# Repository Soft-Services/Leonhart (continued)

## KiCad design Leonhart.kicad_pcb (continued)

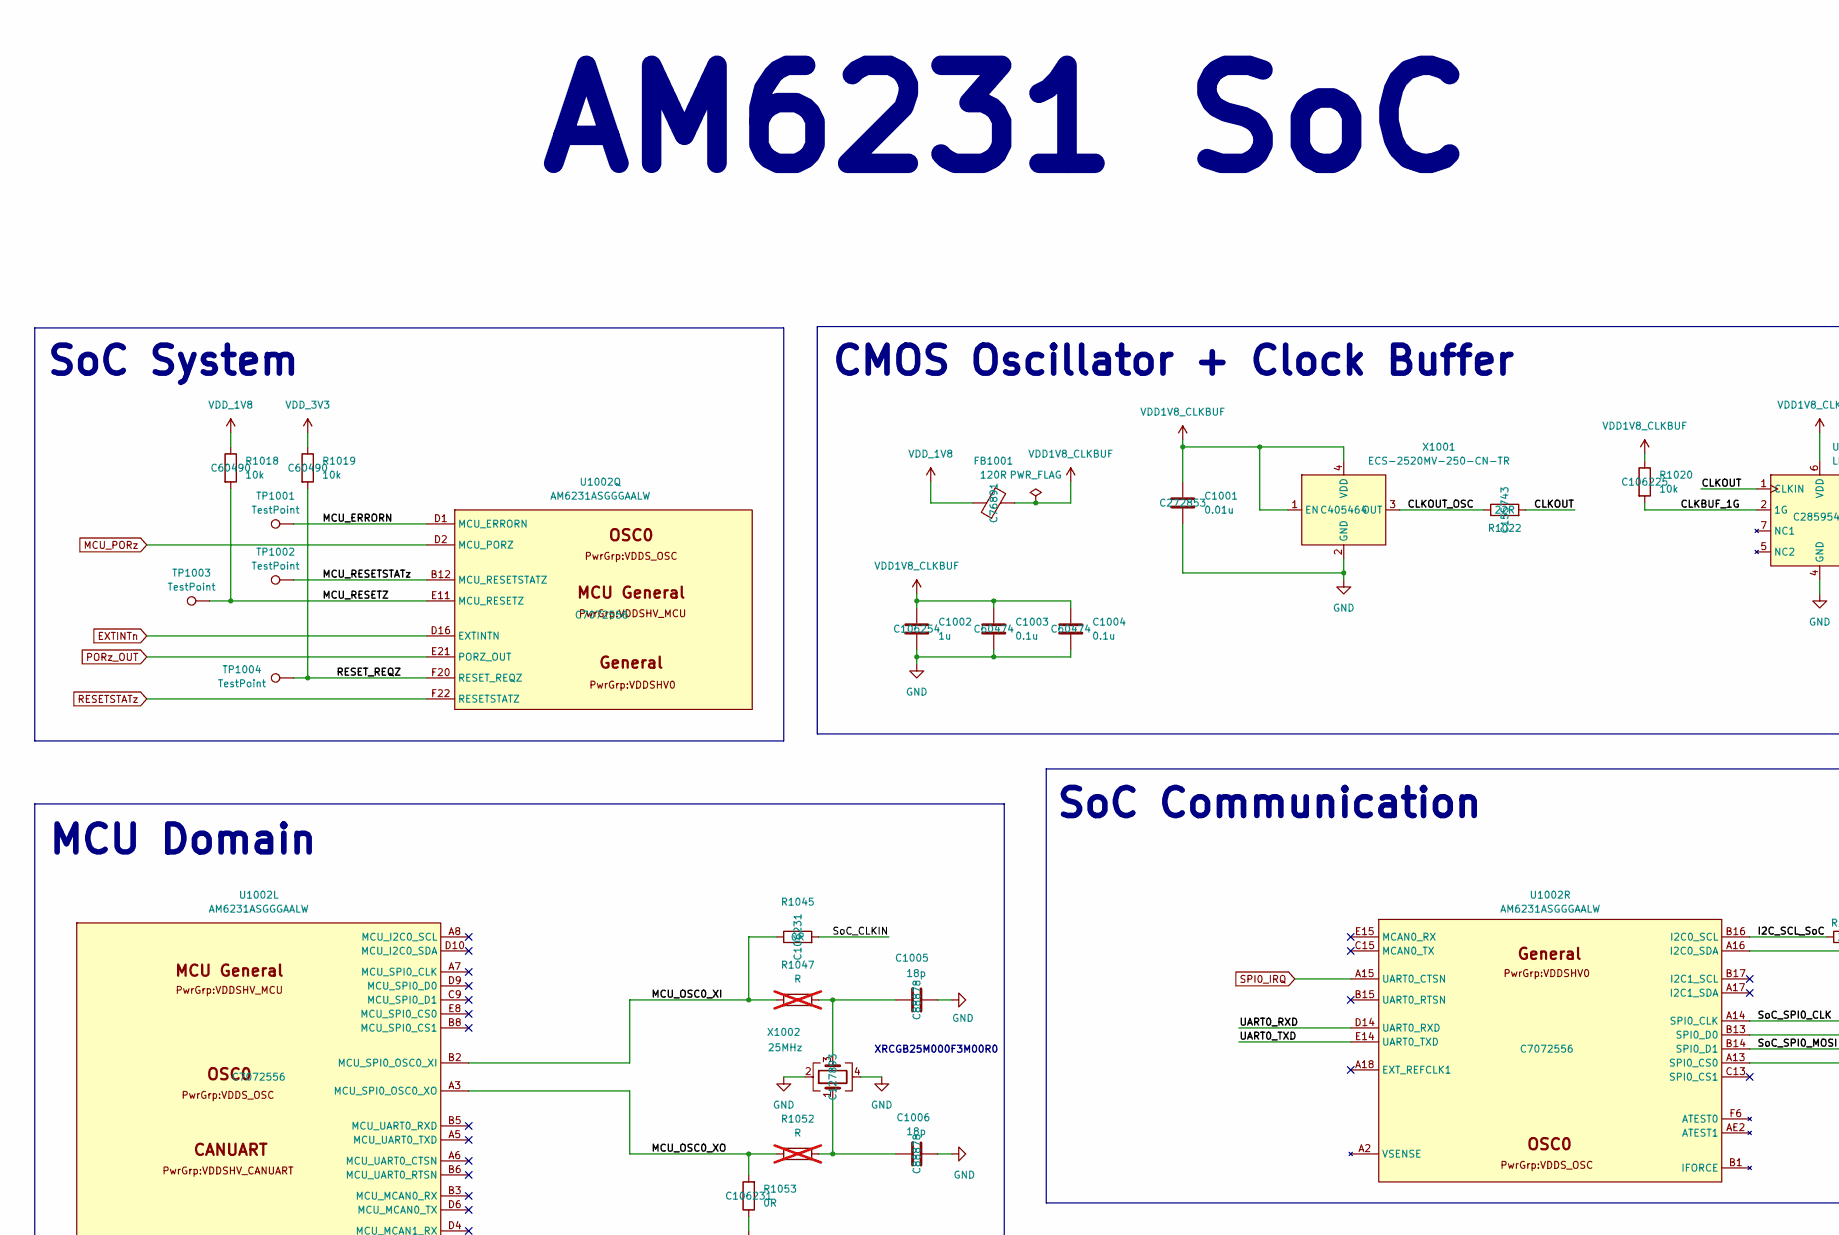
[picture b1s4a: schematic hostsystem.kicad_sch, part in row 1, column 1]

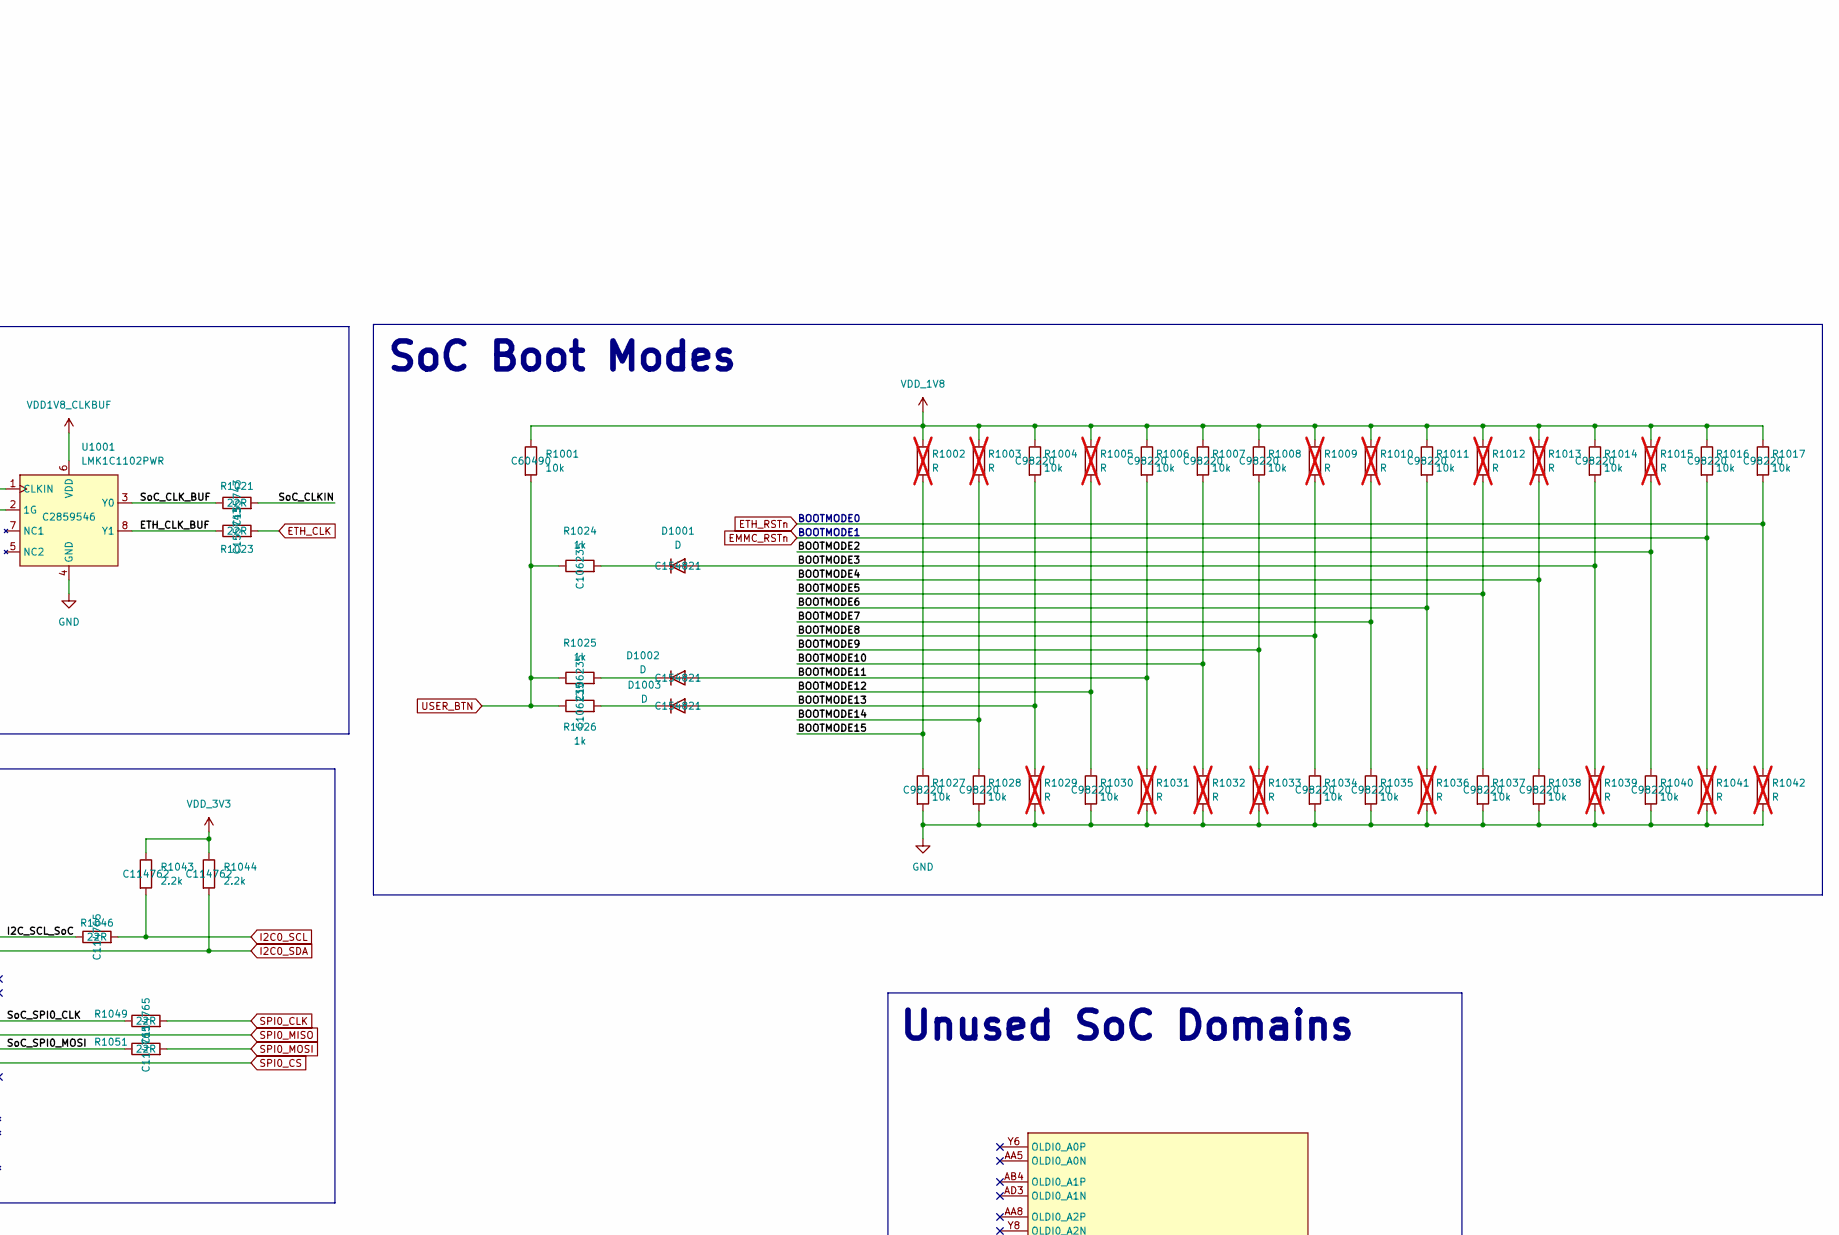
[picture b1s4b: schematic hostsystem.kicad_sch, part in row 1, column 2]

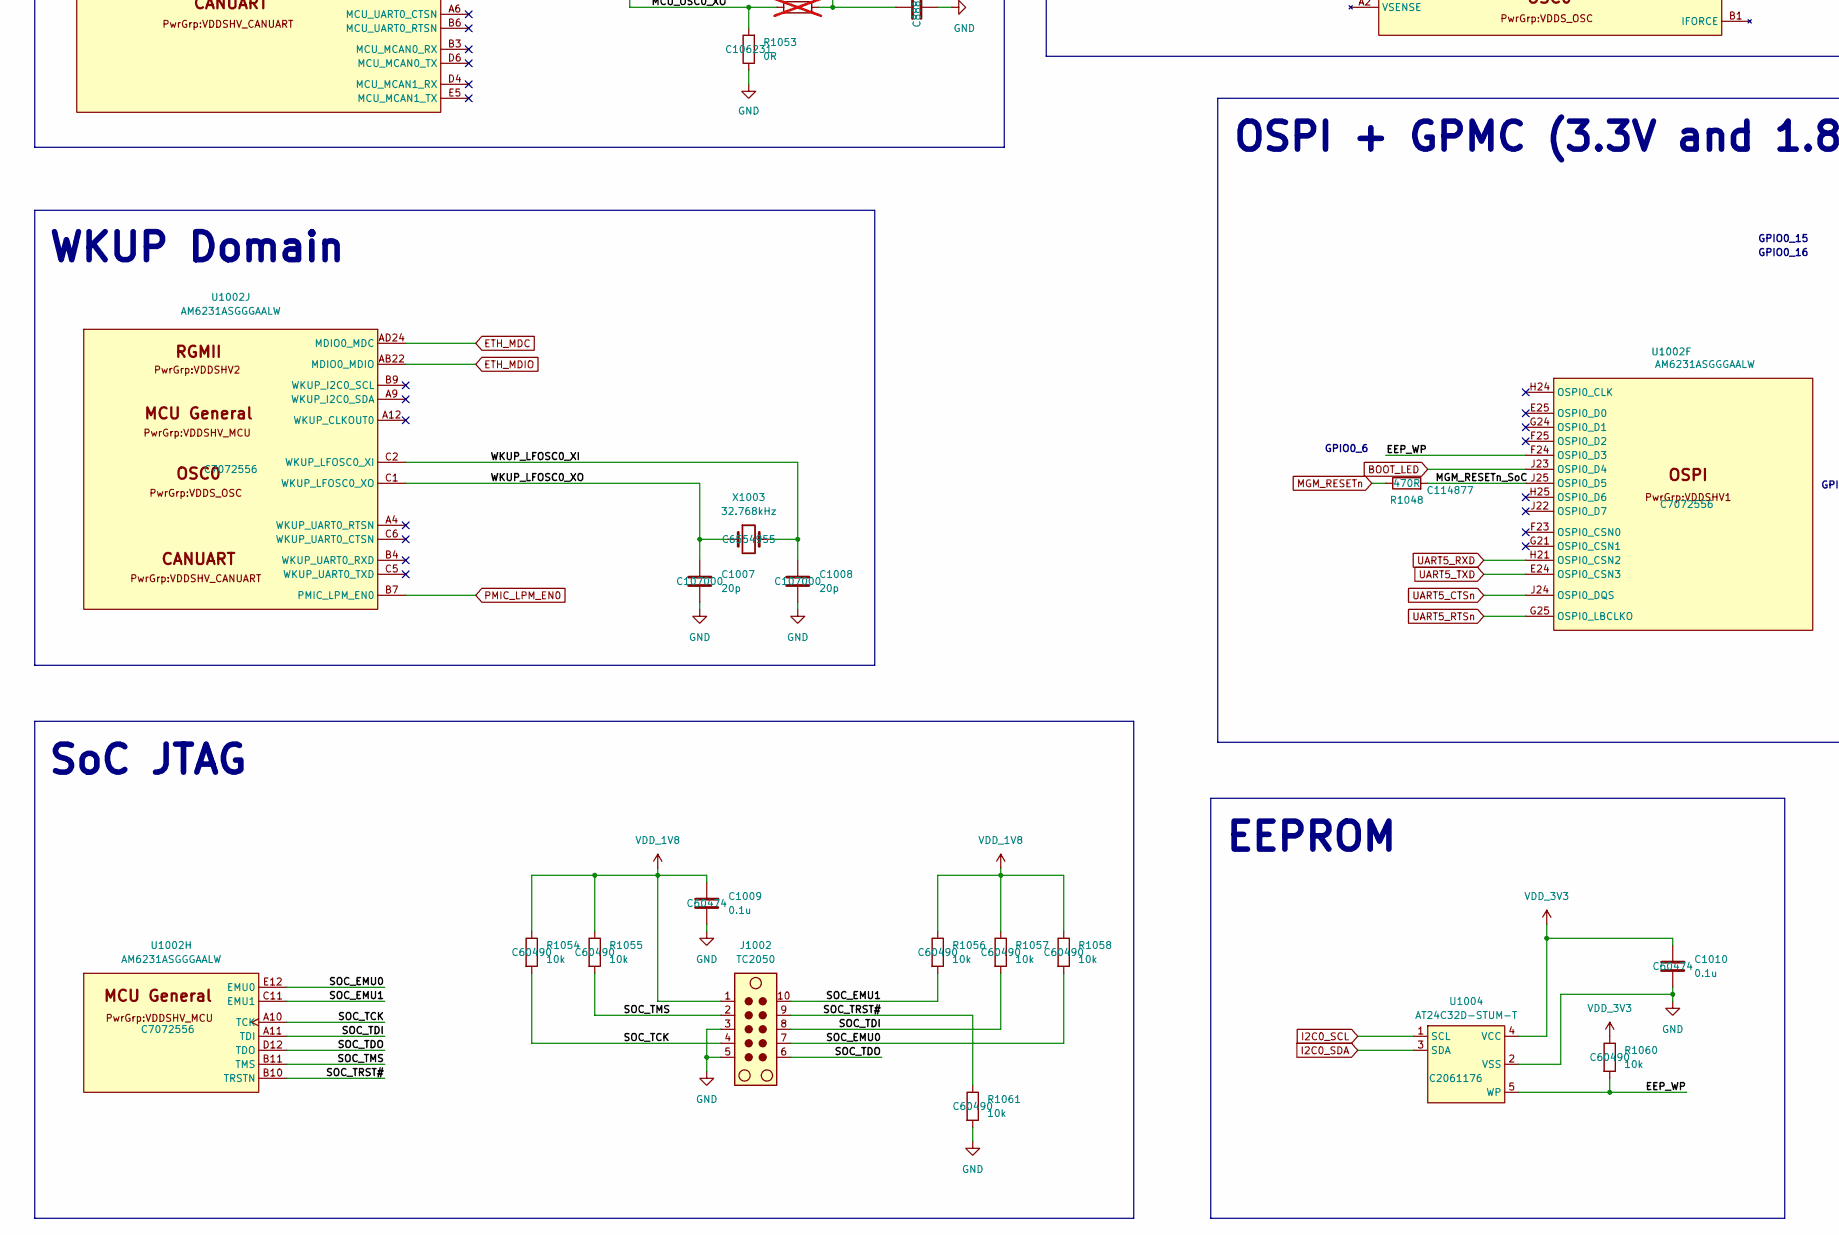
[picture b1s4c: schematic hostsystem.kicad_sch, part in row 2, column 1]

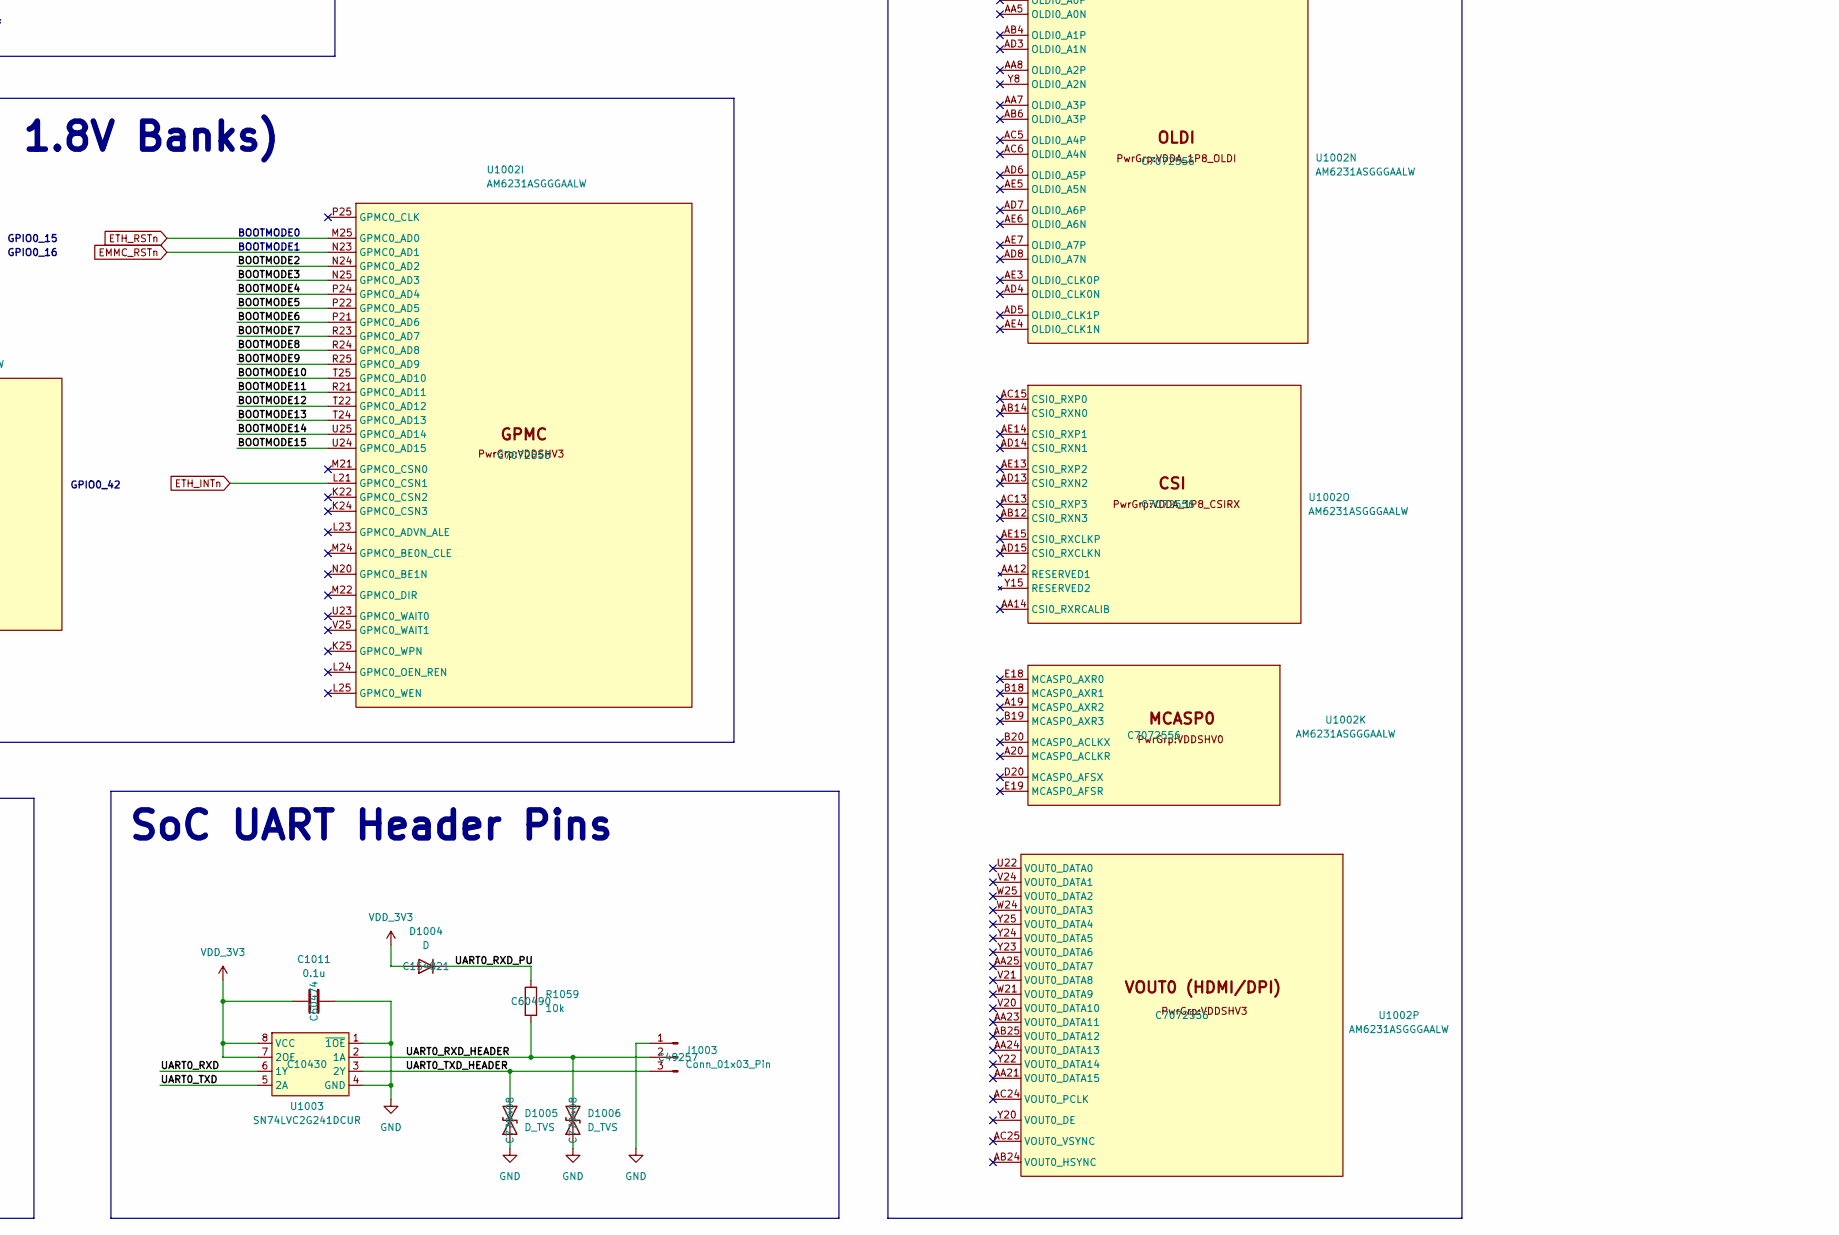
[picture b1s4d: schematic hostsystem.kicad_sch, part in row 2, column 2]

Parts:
C1001: 0.01u; C_0201_0603Metric; JLCPCB Part# C272853
C1002: 1u; C_0402_1005Metric; JLCPCB Part# C106254
C1003, C1004, C1009, C1010, C1011: 0.1u; C_0402_1005Metric; JLCPCB Part# C60474
C1005, C1006: 18p; C_0402_1005Metric; JLCPCB Part# C88878
C1007, C1008: 20p; C_0402_1005Metric; JLCPCB Part# C107000
D1001, D1002, D1003, D1004: D; D_SOD-523; JLCPCB Part# C154821
D1005, D1006: D_TVS; TPD1E1B04DPYR; JLCPCB Part# C779408
FB1001: 120R; R_0402_1005Metric; JLCPCB Part# C76891
J1002: TC2050; Tag-Connect_TC2050-IDC-FP_2x05_P1.27mm_Vertical
J1003: Conn_01x03_Pin; PinHeader_1x03_P2.54mm_Vertical; JLCPCB Part# C49257
R1001, R1018, R1019, R1054, R1055, R1056, R1057, R1058, R1059, R1060, R1061: 10k; R_0402_1005Metric; JLCPCB Part# C60490
R1002, R1003, R1005, R1009, R1010, R1012, R1013, R1015, R1029, R1031, R1032, R1033, R1036, R1039, R1041, R1042: R; R_0603_1608Metric; not fitted
R1004, R1006, R1007, R1008, R1011, R1014, R1016, R1017, R1027, R1028, R1030, R1034, R1035, R1037, R1038, R1040: 10k; R_0603_1608Metric; JLCPCB Part# C98220
R1020: 10k; R_0201_0603Metric; JLCPCB Part# C106225
R1021, R1022, R1023: 22R; R_0201_0603Metric; JLCPCB Part# C155743
R1024, R1025, R1026: 1k; R_0402_1005Metric; JLCPCB Part# C106235
R1043, R1044: 2.2k; R_0402_1005Metric; JLCPCB Part# C114762
R1045, R1053: 0R; R_0402_1005Metric; JLCPCB Part# C106231
R1046, R1049, R1051: 22R; R_0402_1005Metric; JLCPCB Part# C114765
R1047, R1052: R; R_0402_1005Metric; not fitted
R1048: 470R; R_0402_1005Metric; JLCPCB Part# C114877
TP1001, TP1002, TP1003, TP1004: TestPoint; TestPoint_Pad_1.0x1.0mm
U1001: LMK1C1102PWR; SOP65P640X120-8N; JLCPCB Part# C2859546
U1002: AM6231ASGGGAALW; BGA425C50P25X25_1300X1300X89; JLCPCB Part# C7072556
U1003: SN74LVC2G241DCUR; SOP50P310X90-8N; JLCPCB Part# C10430
U1004: AT24C32D-STUM-T; SOT-23-5; JLCPCB Part# C2061176
X1001: ECS-2520MV-250-CN-TR; ECS2520MV250CNTR; JLCPCB Part# C405464
X1002: 25MHz; Crystal_SMD_2016-4Pin_2.0x1.6mm; JLCPCB Part# C127893
X1003: 32.768kHz; FC-135R 32.7680KA-A3; JLCPCB Part# C6554955

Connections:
/Host System [1]/BOOTMODE2: R1015.2, R1040.1, U1002.N24 (GPMC0_AD2)
/Host System [1]/BOOTMODE3: D1001.2 (A), R1014.2, R1039.1, U1002.N25 (GPMC0_AD3)
/Host System [1]/BOOTMODE4: R1013.2, R1038.1, U1002.P24 (GPMC0_AD4)
/Host System [1]/BOOTMODE5: R1012.2, R1037.1, U1002.P22 (GPMC0_AD5)
/Host System [1]/BOOTMODE6: R1011.2, R1036.1, U1002.P21 (GPMC0_AD6)
/Host System [1]/BOOTMODE7: R1010.2, R1035.1, U1002.R23 (GPMC0_AD7)
/Host System [1]/BOOTMODE8: R1009.2, R1034.1, U1002.R24 (GPMC0_AD8)
/Host System [1]/BOOTMODE9: R1008.2, R1033.1, U1002.R25 (GPMC0_AD9)
/Host System [1]/BOOTMODE10: R1007.2, R1032.1, U1002.T25 (GPMC0_AD10)
/Host System [1]/BOOTMODE11: D1002.2 (A), R1006.2, R1031.1, U1002.R21 (GPMC0_AD11)
/Host System [1]/BOOTMODE12: R1005.2, R1030.1, U1002.T22 (GPMC0_AD12)
/Host System [1]/BOOTMODE13: D1003.2 (A), R1004.2, R1029.1, U1002.T24 (GPMC0_AD13)
/Host System [1]/BOOTMODE14: R1003.2, R1028.1, U1002.U25 (GPMC0_AD14)
/Host System [1]/BOOTMODE15: R1002.2, R1027.1, U1002.U24 (GPMC0_AD15)
/Host System [1]/CLKBUF_1G: R1020.2, U1001.2 (1G)
/Host System [1]/CLKOUT: R1022.2, U1001.1 (CLKIN)
/Host System [1]/CLKOUT_OSC: R1022.1, X1001.3 (OUT)
/Host System [1]/EEP_WP: R1060.2, U1002.F24 (OSPI0_D3), U1004.5 (WP)
/Host System [1]/ETH_CLK_BUF: R1023.1, U1001.8 (Y1)
/Host System [1]/I2C_SCL_SoC: R1046.1, U1002.B16 (I2C0_SCL)
/Host System [1]/MCU_ERRORN: TP1001.1, U1002.D1 (MCU_ERRORN)
/Host System [1]/MCU_OSC0_XI: R1045.1, R1047.1, U1002.B2 (MCU_SPI0_OSC0_XI)
/Host System [1]/MCU_OSC0_XO: R1052.1, R1053.2, U1002.A3 (MCU_SPI0_OSC0_XO)
/Host System [1]/MCU_RESETSTATz: TP1002.1, U1002.B12 (MCU_RESETSTATZ)
/Host System [1]/MCU_RESETZ: R1018.2, TP1003.1, U1002.E11 (MCU_RESETZ)
/Host System [1]/MGM_RESETn_SoC: R1048.2, U1002.J25 (OSPI0_D5)
/Host System [1]/RESET_REQZ: R1019.2, TP1004.1, U1002.F20 (RESET_REQZ)
/Host System [1]/SOC_EMU0: J1002.7, R1058.2, U1002.E12 (EMU0)
/Host System [1]/SOC_EMU1: J1002.10, R1056.2, U1002.C11 (EMU1)
/Host System [1]/SOC_TCK: J1002.4, R1054.2, U1002.A10 (TCK)
/Host System [1]/SOC_TDI: J1002.8, R1057.2, U1002.A11 (TDI)
/Host System [1]/SOC_TDO: J1002.6, U1002.D12 (TDO)
/Host System [1]/SOC_TMS: J1002.2, R1055.2, U1002.B11 (TMS)
/Host System [1]/SOC_TRST#: J1002.9, R1061.1, U1002.B10 (TRSTN)
/Host System [1]/SoC_CLKIN: R1021.2, R1045.2
/Host System [1]/SoC_CLK_BUF: R1021.1, U1001.3 (Y0)
/Host System [1]/SoC_SPI0_CLK: R1049.1, U1002.A14 (SPI0_CLK)
/Host System [1]/SoC_SPI0_MOSI: R1051.1, U1002.B14 (SPI0_D1)
/Host System [1]/UART0_RXD: U1002.D14 (UART0_RXD), U1003.6 (1Y)
/Host System [1]/UART0_RXD_HEADER: D1006.2 (A2), J1003.2, R1059.2, U1003.2 (1A)
/Host System [1]/UART0_RXD_PU: D1004.1 (K), R1059.1
/Host System [1]/UART0_TXD: U1002.E14 (UART0_TXD), U1003.5 (2A)
/Host System [1]/UART0_TXD_HEADER: D1005.2 (A2), J1003.3, U1003.3 (2Y)
/Host System [1]/WKUP_LFOSC0_XI: C1008.1, U1002.C2 (WKUP_LFOSC0_XI), X1003.2
/Host System [1]/WKUP_LFOSC0_XO: C1007.1, U1002.C1 (WKUP_LFOSC0_XO), X1003.1
BOOT_LED: U1002.J23 (OSPI0_D4); also elsewhere on the board
EMMC_RSTn: R1016.2, R1041.1, U1002.N23 (GPMC0_AD1); also elsewhere on the board
ETH_CLK: R1023.2; also elsewhere on the board
ETH_INTn: U1002.L21 (GPMC0_CSN1); also elsewhere on the board
ETH_MDC: U1002.AD24 (MDIO0_MDC); also elsewhere on the board
ETH_MDIO: U1002.AB22 (MDIO0_MDIO); also elsewhere on the board
ETH_RSTn: R1017.2, R1042.1, U1002.M25 (GPMC0_AD0); also elsewhere on the board
EXTINTn: U1002.D16 (EXTINTN); also elsewhere on the board
GND: C1001.2, C1002.2, C1003.2, C1004.2, C1005.2, C1006.2, C1007.2, C1008.2, C1009.2, C1010.2, C1011.2, D1005.1 (A1), D1006.1 (A1), J1002.3, J1002.5, J1003.1, R1027.2, R1028.2, R1029.2, R1030.2, R1031.2, R1032.2, R1033.2, R1034.2, R1035.2, R1036.2, R1037.2, R1038.2, R1039.2, R1040.2, R1041.2, R1042.2, R1053.1, R1061.2, U1001.4 (GND), U1003.1 (~1OE), U1003.4 (GND), U1004.2 (VSS), X1001.2 (GND), X1002.2, X1002.4; also elsewhere on the board
I2C0_SCL: R1043.2, R1046.2, U1004.1 (SCL); also elsewhere on the board
I2C0_SDA: R1044.2, U1002.A16 (I2C0_SDA), U1004.3 (SDA); also elsewhere on the board
MCU_PORz: U1002.D2 (MCU_PORZ); also elsewhere on the board
MGM_RESETn: R1048.1; also elsewhere on the board
unnamed: C1005.1, R1047.2, X1002.3
unnamed: C1006.1, R1052.2, X1002.1
unnamed: D1001.1 (K), R1024.2
unnamed: D1002.1 (K), R1025.2
unnamed: D1003.1 (K), R1026.2
PMIC_LPM_EN0: U1002.B7 (PMIC_LPM_EN0); also elsewhere on the board
PORz_OUT: U1002.E21 (PORZ_OUT); also elsewhere on the board
RESETSTATz: U1002.F22 (RESETSTATZ); also elsewhere on the board
SPI0_CLK: R1049.2; also elsewhere on the board
SPI0_CS: U1002.A13 (SPI0_CS0); also elsewhere on the board
SPI0_IRQ: U1002.A15 (UART0_CTSN); also elsewhere on the board
SPI0_MISO: U1002.B13 (SPI0_D0); also elsewhere on the board
SPI0_MOSI: R1051.2; also elsewhere on the board
UART5_CTSn: U1002.J24 (OSPI0_DQS); also elsewhere on the board
UART5_RTSn: U1002.G25 (OSPI0_LBCLKO); also elsewhere on the board
UART5_RXD: U1002.H21 (OSPI0_CSN2); also elsewhere on the board
UART5_TXD: U1002.E24 (OSPI0_CSN3); also elsewhere on the board
USER_BTN: R1001.2, R1024.1, R1025.1, R1026.1; also elsewhere on the board
VDD1V8_CLKBUF: C1001.1, C1002.1, C1003.1, C1004.1, FB1001.2, R1020.1, U1001.6 (VDD), X1001.1 (EN), X1001.4 (VDD)
VDD_1V8: C1009.1, FB1001.1, J1002.1, R1001.1, R1002.1, R1003.1, R1004.1, R1005.1, R1006.1, R1007.1, R1008.1, R1009.1, R1010.1, R1011.1, R1012.1, R1013.1, R1014.1, R1015.1, R1016.1, R1017.1, R1018.1, R1054.1, R1055.1, R1056.1, R1057.1, R1058.1; also elsewhere on the board
VDD_3V3: C1010.1, C1011.1, D1004.2 (A), R1019.1, R1043.1, R1044.1, R1060.1, U1003.7 (2OE), U1003.8 (VCC), U1004.4 (VCC); also elsewhere on the board

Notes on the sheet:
AM6231 SoC
BOOTMODE1
CMOS Oscillator + Clock Buffer
BOOTMODE0
MCU Domain
GPIO0_42
GPIO0_6
WKUP Domain
OSPI + GPMC (3.3V and 1.8V Banks)
SoC System
SoC Boot Modes
EEPROM
Unused SoC Domains
SoC JTAG
SoC Communication
GPIO0_15
XRCGB25M000F3M00R0
GPIO0_16
SoC UART Header Pins

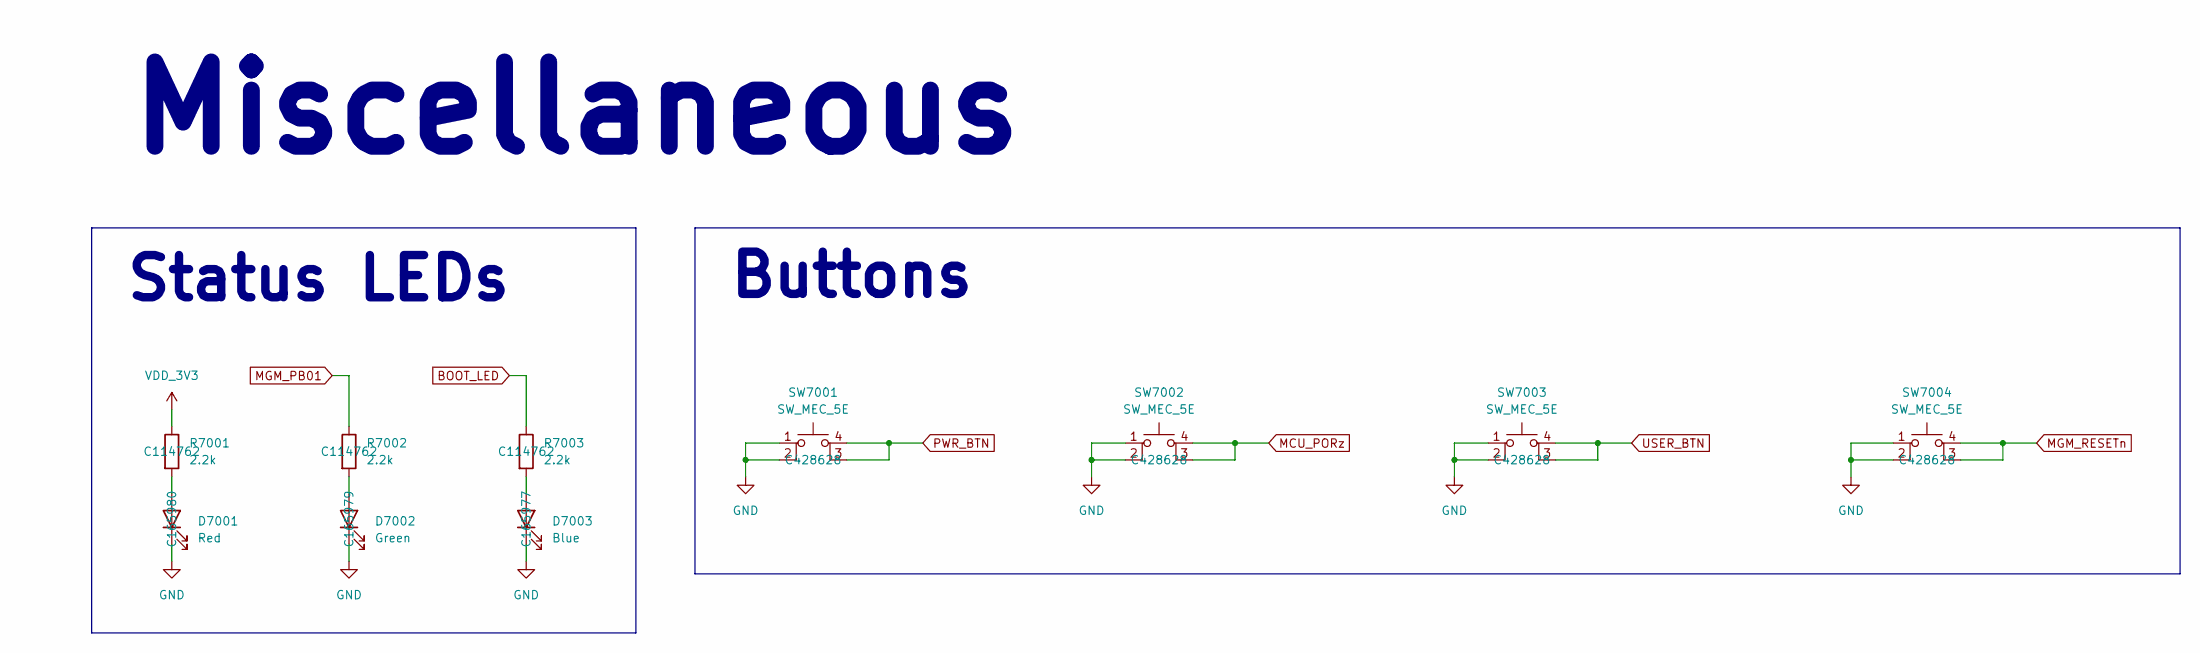
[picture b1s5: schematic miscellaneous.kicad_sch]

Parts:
D7001: Red; LED_0402_1005Metric; JLCPCB Part# C165980
D7002: Green; LED_0402_1005Metric; JLCPCB Part# C165979
D7003: Blue; LED_0402_1005Metric; JLCPCB Part# C165977
R7001, R7002, R7003: 2.2k; R_0402_1005Metric; JLCPCB Part# C114762
SW7001, SW7002, SW7003, SW7004: SW_MEC_5E; 1825910-6; JLCPCB Part# C428628

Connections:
BOOT_LED: R7003.1; also elsewhere on the board
GND: D7001.1 (K), D7002.1 (K), D7003.1 (K), SW7001.1, SW7001.2, SW7002.1, SW7002.2, SW7003.1, SW7003.2, SW7004.1, SW7004.2; also elsewhere on the board
MCU_PORz: SW7002.3 (K), SW7002.4 (A); also elsewhere on the board
MGM_PB01: R7002.1; also elsewhere on the board
MGM_RESETn: SW7004.3 (K), SW7004.4 (A); also elsewhere on the board
unnamed: D7001.2 (A), R7001.2
unnamed: D7002.2 (A), R7002.2
unnamed: D7003.2 (A), R7003.2
PWR_BTN: SW7001.3 (K), SW7001.4 (A); also elsewhere on the board
USER_BTN: SW7003.3 (K), SW7003.4 (A); also elsewhere on the board
VDD_3V3: R7001.1; also elsewhere on the board

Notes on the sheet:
Buttons
Miscellaneous
Status LEDs
